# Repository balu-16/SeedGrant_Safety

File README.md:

# Smart Safety Tag

Personal-safety project: Expo / React Native client + FastAPI + PostgreSQL (Supabase) backend + React admin portal.

## Layout

- `client/` — Expo / React Native / TypeScript app (onboarding, auth, Home, Track, Guardians, Profile). See `client/README.md`.
- `server/` — FastAPI + PostgreSQL (Supabase) backend, shared by the app and the admin portal. See `server/README.md` for setup, migrations, and the API surface.
- `admin/` — React + Vite web admin portal (same design language as the app). See `admin/README.md`.
- `reference/` — original design reference images (unchanged).

Browser-test output (screenshots, traces) is generated under `client/test-results/`
and is git-ignored.

## Quick start

Frontend (mobile app):

```sh
cd client
npm install
npx expo start
```

Backend:

```sh
cd server
uv sync
cp .env.example .env   # then fill in DATABASE_URL + JWT_SECRET
uv run python -m app.db.migrate
uv run uvicorn app.main:app --reload   # http://127.0.0.1:8000
```

Admin portal (web):

```sh
cd admin
npm install
npm run dev   # http://localhost:5173, proxies /api to localhost:8000
```

## Admin portal

- Same backend, same database — the portal adds `/api/admin/*` routes guarded by a
  `role` column on `users` (fail-closed, checked per request).
- First admin: set `ADMIN_EMAILS=email@example.com` on the server (promoted at
  startup), or run `uv run python -m app.bootstrap_admin email@example.com` once.
- Features: dashboard KPIs + charts, live SOS monitor (WebSocket), full user
  control (disable / force-logout / reset-password / promote / delete), device and
  guardian management, emergency timelines on a map, location history + purge,
  push broadcasts, and a complete audit log.
- Deploy: static build (`admin/dist`) — e.g. Vercel (config included). Set
  `VITE_API_URL` to the backend URL and add the portal origin to the server's
  `CORS_ORIGINS`.

## Deploy (Render)

Root Directory: `server`. See `server/README.md` for build/start commands and env vars.

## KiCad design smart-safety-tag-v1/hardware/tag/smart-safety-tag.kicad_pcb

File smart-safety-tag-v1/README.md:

# Smart Safety Tag V1

Editable KiCad design and prototype fabrication package for a BLE safety tag and its protected pogo charging adapter. The tag uses an ESP32-S3-MINI-1-N4R2, PDM microphone, LIS2DW12, MAX17048, protected 400 mAh battery, physical SOS button, RGB LED and vibration motor. The phone supplies GPS and Internet access.

Both boards are routed and checked with KiCad 10.0.6. PCB DRC has no ignored rules, violations, unconnected items or schematic-parity findings. ERC reports have zero errors and warnings under KiCad's default checks; the four ERC diagnostics listed in each report remain ignored by KiCad. No individual ERC/DRC findings are excluded. The hardware-test application builds with ESP-IDF v5.5. **Physical prototype validation remains pending.** This package supports prototype manufacture; it does not establish product safety, radio/acoustic performance, enclosure fit or an ingress-protection rating.

| Deliverable | Location |
| --- | --- |
| Tag KiCad project, 8 hierarchical child sheets and 60 × 42 mm PCB | [hardware/tag/smart-safety-tag.kicad_pro](hardware/tag/smart-safety-tag.kicad_pro) |
| Charging adapter KiCad project and 32 × 22 mm PCB | [hardware/charging-adapter/charging-adapter.kicad_pro](hardware/charging-adapter/charging-adapter.kicad_pro) |
| Tag Gerbers/drills, BOM, placement CSVs and assembly/schematic PDFs | [manufacturing/tag](manufacturing/tag) |
| Adapter Gerbers/drills, BOM, placement CSVs and assembly/schematic PDFs | [manufacturing/charging-adapter](manufacturing/charging-adapter) |
| Component decisions, substitutions and manufacturer sources | [docs/design-inputs.md](docs/design-inputs.md) |
| Power architecture and calculated runtime scenarios | [docs/power-budget.md](docs/power-budget.md) |
| GPIO map and six-pad programming interface | [docs/gpio-map.md](docs/gpio-map.md) |
| Board fabrication and assembly specification | [docs/manufacturing-specification.md](docs/manufacturing-specification.md) |
| Power-on, charging, peripheral and qualification procedure | [docs/bring-up.md](docs/bring-up.md) |
| CAD/calculation/build evidence and pending measurements | [docs/verification.md](docs/verification.md) |
| Modular hardware-test source and prebuilt images | [firmware/hardware-tests](firmware/hardware-tests) |

Use KiCad 10.0.x or later and keep each project's `symbols/`, `footprints/`, `sym-lib-table` and `fp-lib-table` alongside its native files. All required symbols and land patterns are supplied locally. Optional 3D model references use KiCad's standard model libraries; external STEP models are not bundled. A PCB 3D view does not validate the proposed enclosure or cell clearances.

The main electrical substitutions are TPS63802 for TPS63031 to increase the converter current margin, TPD1E10B06 for the proposed charging ESD diode, and switched 3.0 V supplies for the microphone and motor. An analog NTC window independently inhibits charging. The charging adapter includes a USB-C power input and eFuse before its exposed spring pins. Read the design decisions and fabrication notes before purchasing or assembly.

The tag has 83 PCB footprints, including six programming pads, two bare charging contacts and a wired motor. RT1 is fitted on the rear. The battery is an off-board BOM item and must be insulated and thermally coupled to RT1 as documented. Both boards are 1.0 mm thick; the adapter's USB connector requires 1.0 ±0.10 mm. The module's antenna projects beyond the tag outline and its keepout must remain clear of the battery, clip and magnets.

Each manufacturing directory has a bare-board ZIP and `manifest.json` linking exported files to the complete editable CAD source using SHA-256 hashes. Assembly CSVs use KiCad coordinates/rotations; read the manufacturing specification before importing them. The fabrication ZIP also contains the manufacturing notes.

To regenerate checks and exports from the project root:

```sh
python3 -m pip install -r scripts/requirements.txt
python3 scripts/generate_gpio_header.py
python3 scripts/check_thermal_window.py
python3 scripts/export_manufacturing.py --cli-command kicad-cli
python3 scripts/package_release.py
```

Placement and schematic-generation scripts are construction tools. Rerunning a placement script replaces the corresponding layout, so preserve the routed board and review changes before doing that. GPIO assignments originate in `hardware/board-interface.json`; electrical components and pin/net definitions originate in `scripts/circuit_data.py`, `adapter_data.py`, `parts.py` and `passive_parts.py`.

The included firmware captures audio and checks peripherals. Keyword inference, a custom emergency BLE service, smartphone messaging and sleep/wake behavior need application firmware and physical validation. Continuous keyword detection does not operate in deep sleep in this design.

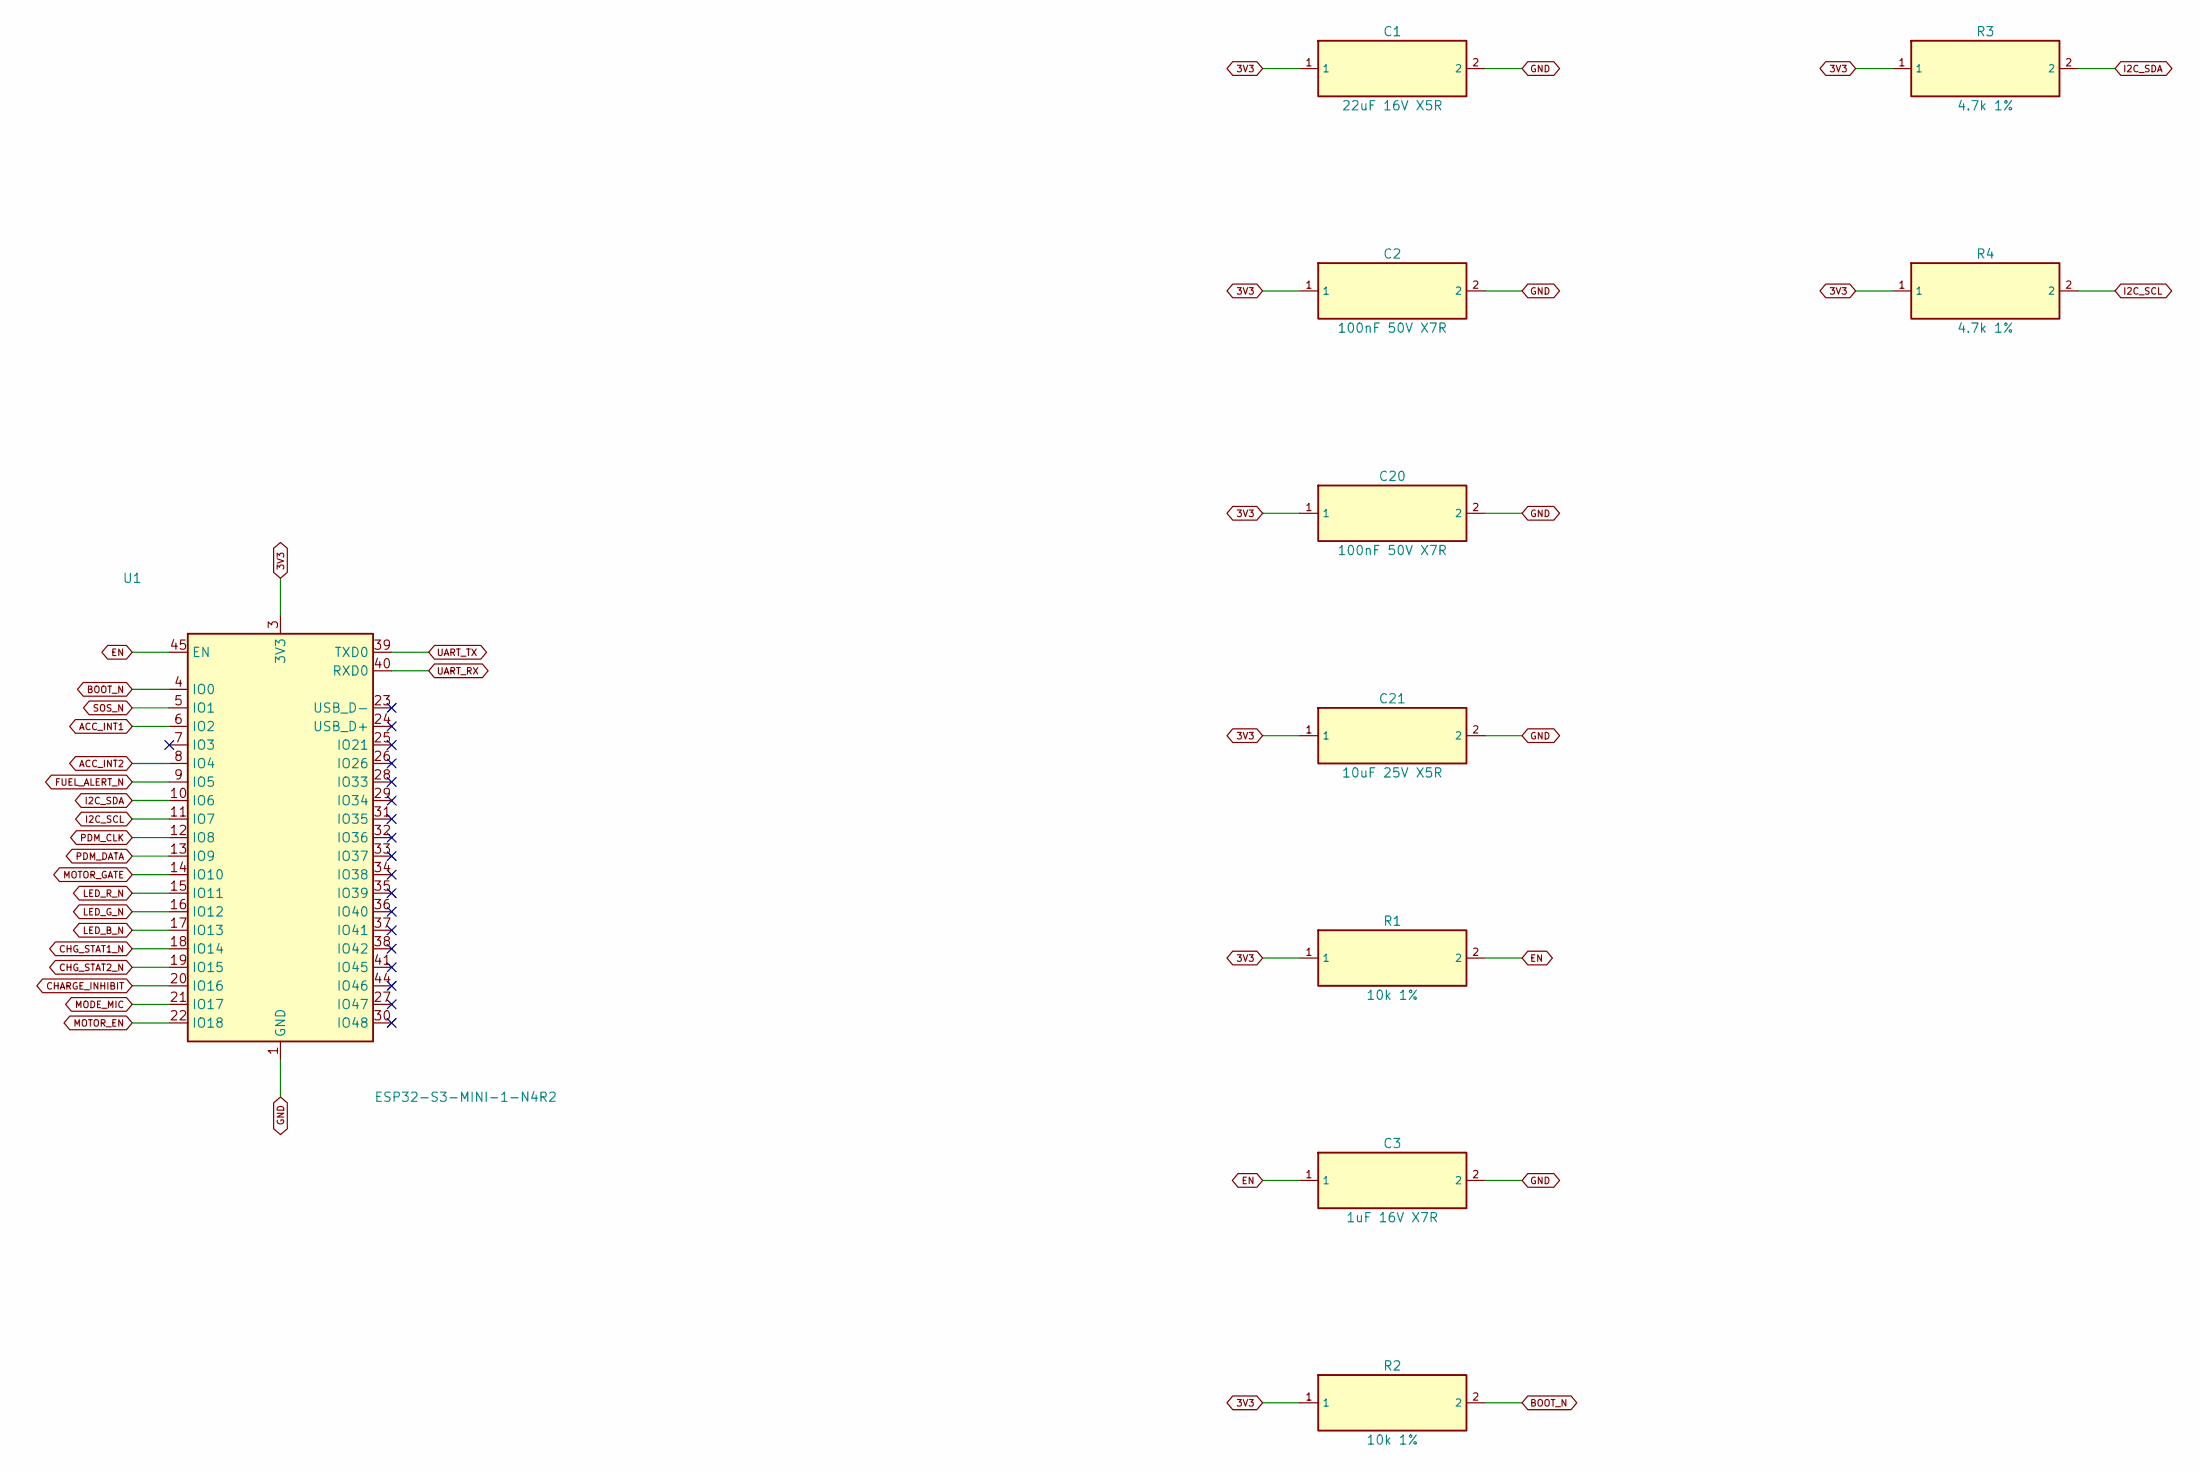
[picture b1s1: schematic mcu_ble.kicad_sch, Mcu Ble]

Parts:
C1: 22uF 16V X5R; C_1206_3216Metric; MPN C3216X5R1C226M160AB
C2, C20: 100nF 50V X7R; C_0603_1608Metric; MPN C1608X7R1H104K080AA
C3: 1uF 16V X7R; C_0603_1608Metric; MPN C1608X7R1C105K080AC
C21: 10uF 25V X5R; C_0805_2012Metric; MPN C2012X5R1E106K125AB
R1, R2: 10k 1%; R_0603_1608Metric; MPN RC0603FR-0710KL
R3, R4: 4.7k 1%; R_0603_1608Metric; MPN RC0603FR-074K7L
U1: ESP32-S3-MINI-1-N4R2; ESP32-S2-MINI-1; MPN ESP32-S3-MINI-1-N4R2

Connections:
3V3: C1.1, C2.1, C20.1, C21.1, R1.1, R2.1, R3.1, R4.1, U1.3 (3V3); also elsewhere on the board
ACC_INT1: U1.6 (IO2); also elsewhere on the board
ACC_INT2: U1.8 (IO4); also elsewhere on the board
BOOT_N: R2.2, U1.4 (IO0); also elsewhere on the board
CHARGE_INHIBIT: U1.20 (IO16); also elsewhere on the board
CHG_STAT1_N: U1.18 (IO14); also elsewhere on the board
CHG_STAT2_N: U1.19 (IO15); also elsewhere on the board
EN: C3.1, R1.2, U1.45 (EN); also elsewhere on the board
FUEL_ALERT_N: U1.9 (IO5); also elsewhere on the board
GND: C1.2, C2.2, C3.2, C20.2, C21.2, U1.1 (GND), U1.2 (GND), U1.42 (GND), U1.43 (GND), U1.46 (GND), U1.47 (GND), U1.48 (GND), U1.49 (GND), U1.50 (GND), U1.51 (GND), U1.52 (GND), U1.53 (GND), U1.54 (GND), U1.55 (GND), U1.56 (GND), U1.57 (GND), U1.58 (GND), U1.59 (GND), U1.60 (GND), U1.61 (GND), U1.62 (GND), U1.63 (GND), U1.64 (GND), U1.65 (GND); also elsewhere on the board
I2C_SCL: R4.2, U1.11 (IO7); also elsewhere on the board
I2C_SDA: R3.2, U1.10 (IO6); also elsewhere on the board
LED_B_N: U1.17 (IO13); also elsewhere on the board
LED_G_N: U1.16 (IO12); also elsewhere on the board
LED_R_N: U1.15 (IO11); also elsewhere on the board
MODE_MIC: U1.21 (IO17); also elsewhere on the board
MOTOR_EN: U1.22 (IO18); also elsewhere on the board
MOTOR_GATE: U1.14 (IO10); also elsewhere on the board
PDM_CLK: U1.12 (IO8); also elsewhere on the board
PDM_DATA: U1.13 (IO9); also elsewhere on the board
SOS_N: U1.5 (IO1); also elsewhere on the board
UART_RX: U1.40 (RXD0); also elsewhere on the board
UART_TX: U1.39 (TXD0); also elsewhere on the board

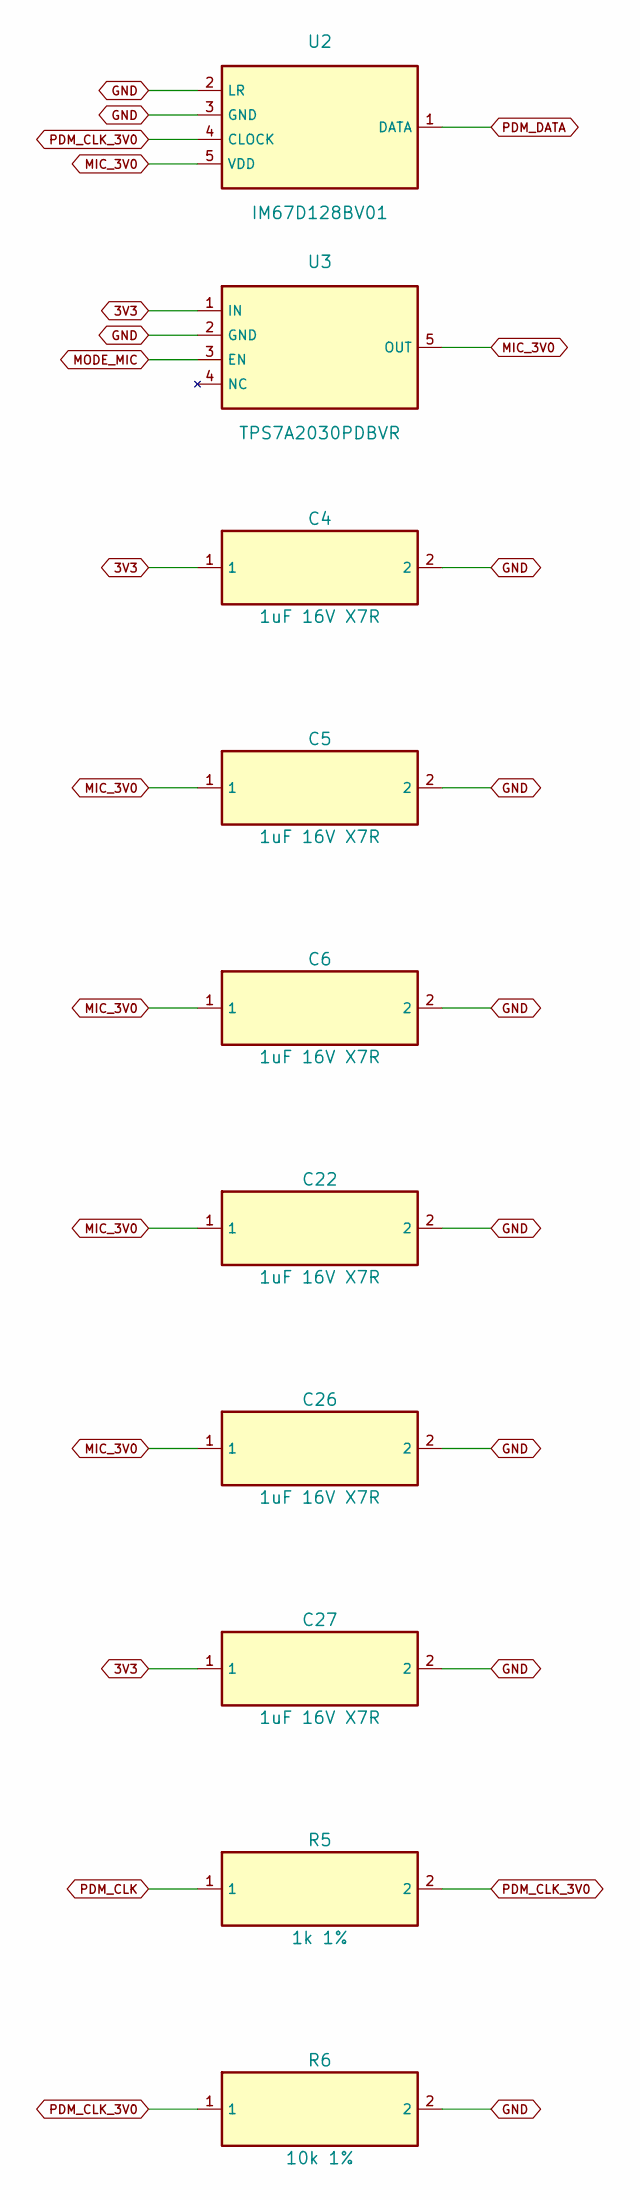
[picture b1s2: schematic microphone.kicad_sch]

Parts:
C4, C5, C6, C22, C26, C27: 1uF 16V X7R; C_0603_1608Metric; MPN C1608X7R1C105K080AC
R5: 1k 1%; R_0603_1608Metric; MPN RC0603FR-071KL
R6: 10k 1%; R_0603_1608Metric; MPN RC0603FR-0710KL
U2: IM67D128BV01; Infineon_IM67D128BV01; MPN IM67D128BV01
U3: TPS7A2030PDBVR; SOT-23-5; MPN TPS7A2030PDBVR

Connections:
3V3: C4.1, C27.1, U3.1 (IN); also elsewhere on the board
GND: C4.2, C5.2, C6.2, C22.2, C26.2, C27.2, R6.2, U2.2 (LR), U2.3 (GND), U3.2 (GND); also elsewhere on the board
MIC_3V0: C5.1, C6.1, C22.1, C26.1, U2.5 (VDD), U3.5 (OUT)
MODE_MIC: U3.3 (EN); also elsewhere on the board
PDM_CLK: R5.1; also elsewhere on the board
PDM_CLK_3V0: R5.2, R6.1, U2.4 (CLOCK)
PDM_DATA: U2.1 (DATA); also elsewhere on the board

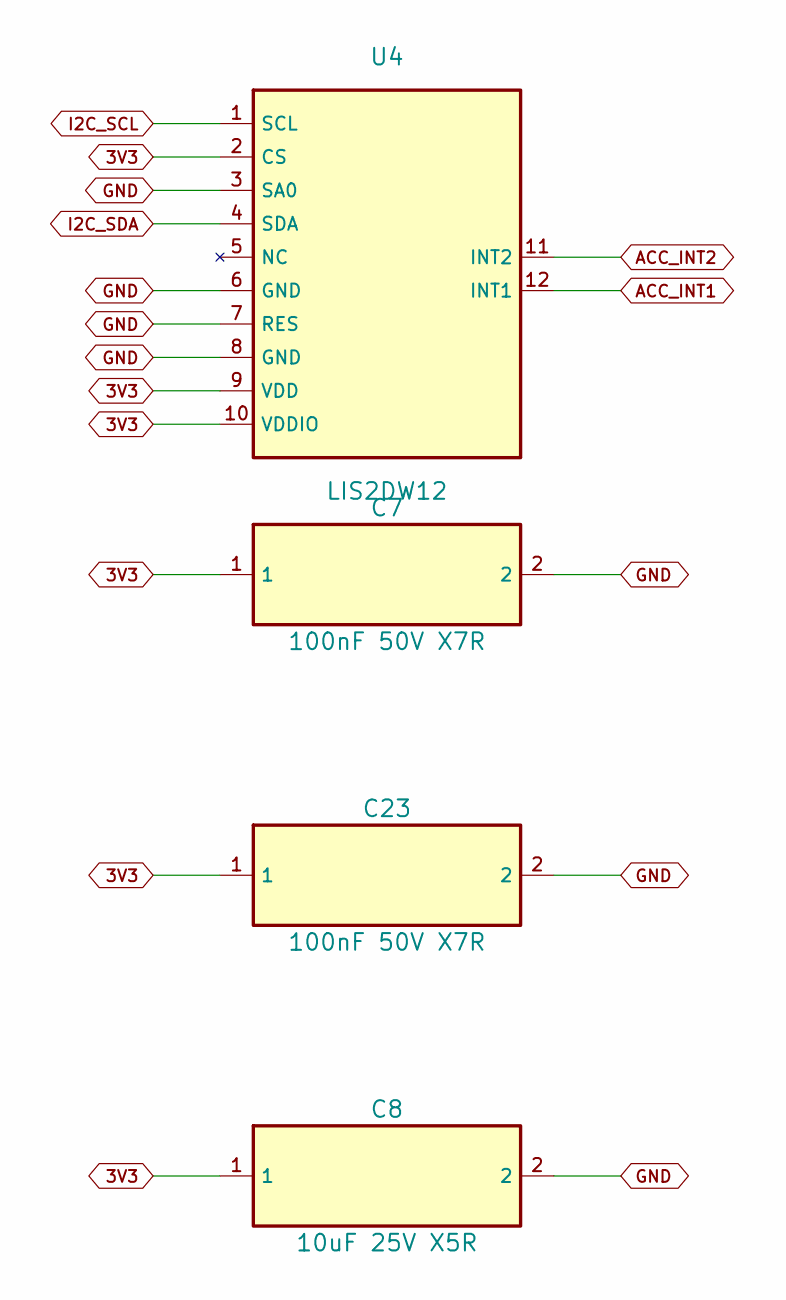
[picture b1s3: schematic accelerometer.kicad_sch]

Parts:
C7, C23: 100nF 50V X7R; C_0603_1608Metric; MPN C1608X7R1H104K080AA
C8: 10uF 25V X5R; C_0805_2012Metric; MPN C2012X5R1E106K125AB
U4: LIS2DW12; LGA-12_2x2mm_P0.5mm; MPN LIS2DW12TR

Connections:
3V3: C7.1, C8.1, C23.1, U4.2 (CS), U4.9 (VDD), U4.10 (VDDIO); also elsewhere on the board
ACC_INT1: U4.12 (INT1); also elsewhere on the board
ACC_INT2: U4.11 (INT2); also elsewhere on the board
GND: C7.2, C8.2, C23.2, U4.3 (SA0), U4.6 (GND), U4.7 (RES), U4.8 (GND); also elsewhere on the board
I2C_SCL: U4.1 (SCL); also elsewhere on the board
I2C_SDA: U4.4 (SDA); also elsewhere on the board

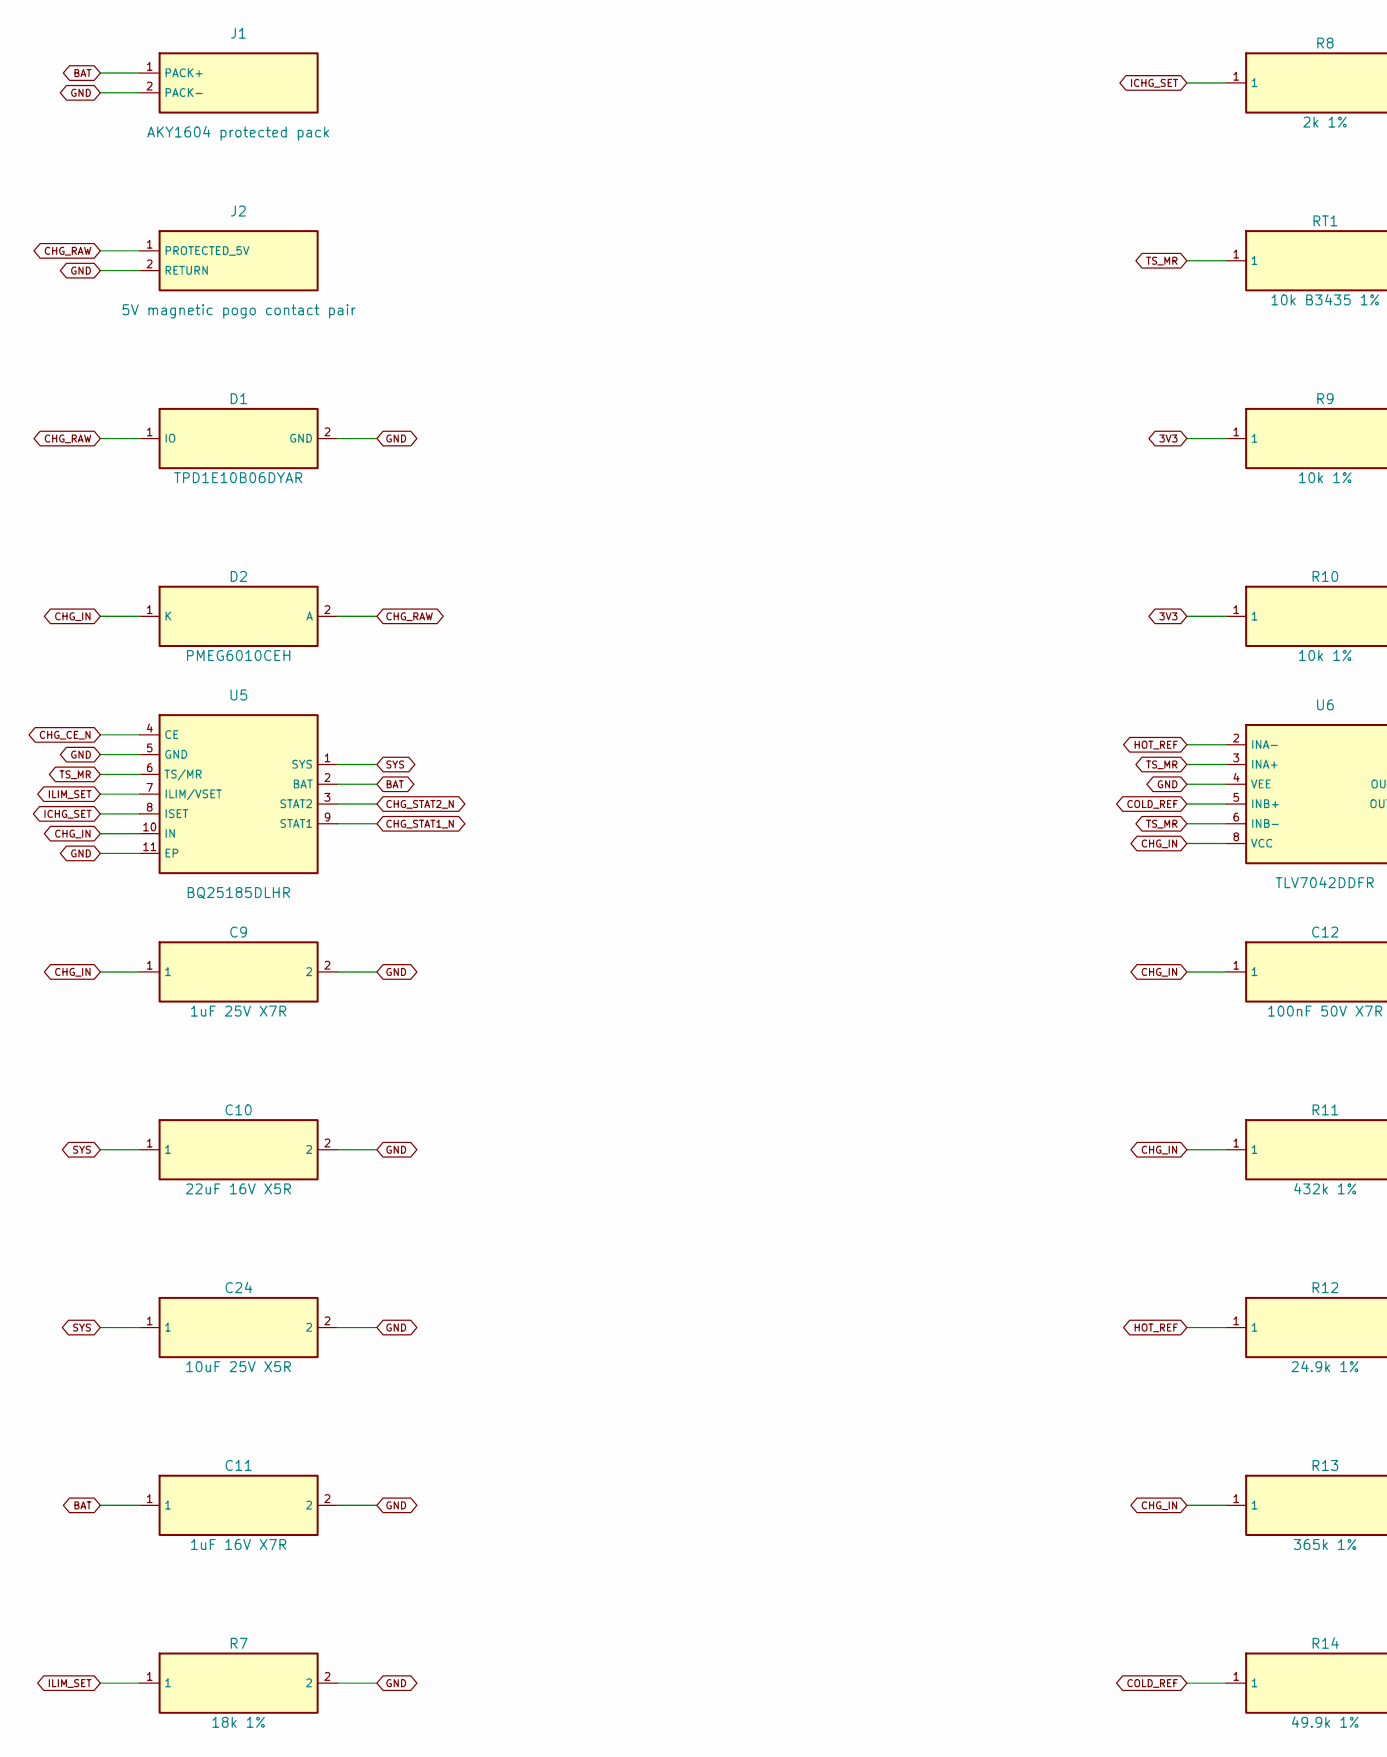
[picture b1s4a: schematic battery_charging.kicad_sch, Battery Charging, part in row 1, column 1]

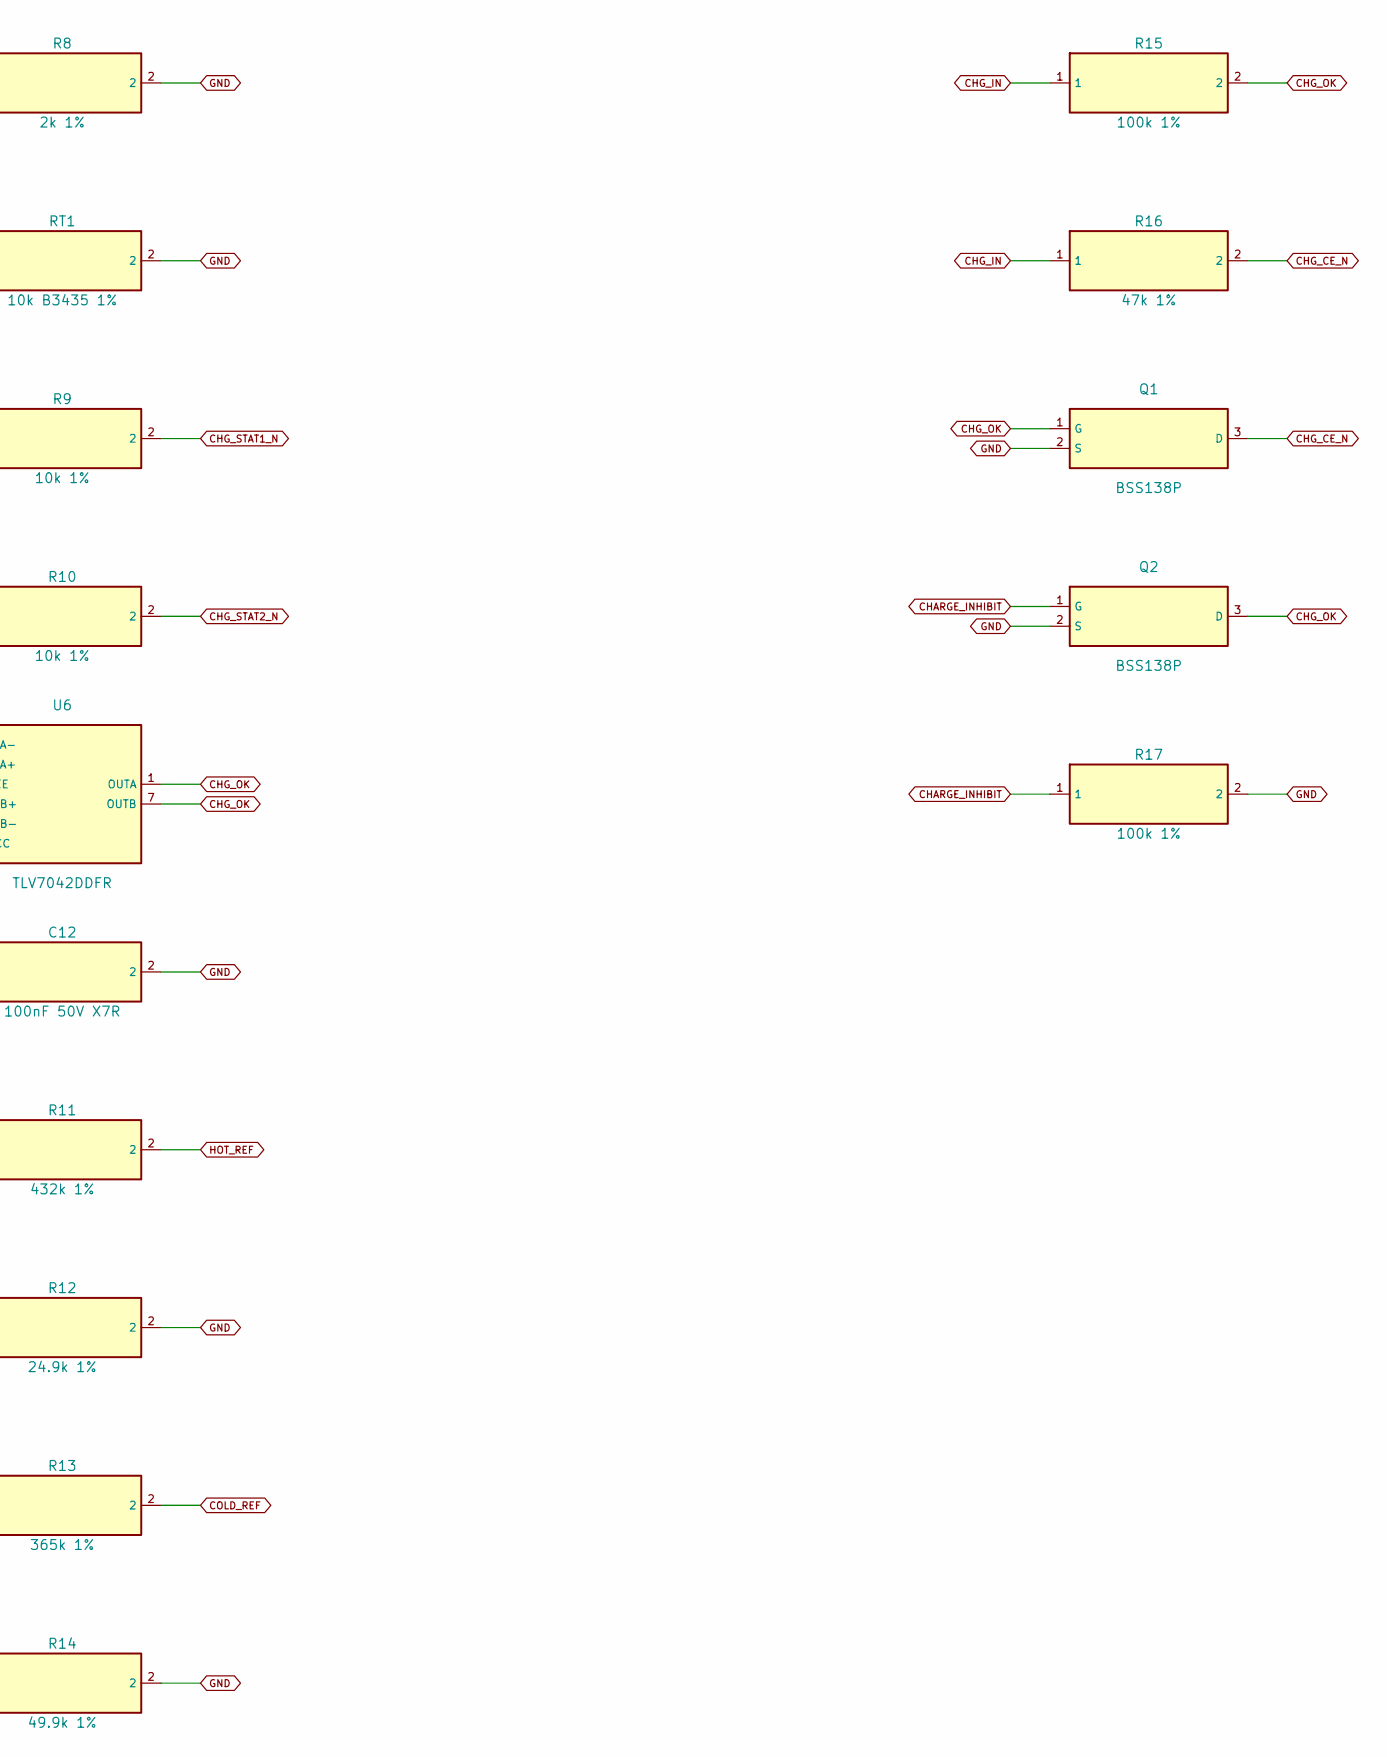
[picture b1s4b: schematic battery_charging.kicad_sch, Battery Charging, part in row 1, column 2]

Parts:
C9: 1uF 25V X7R; C_0603_1608Metric; MPN C1608X7R1E105K080AE
C10: 22uF 16V X5R; C_1206_3216Metric; MPN C3216X5R1C226M160AB
C11: 1uF 16V X7R; C_0603_1608Metric; MPN C1608X7R1C105K080AC
C12: 100nF 50V X7R; C_0603_1608Metric; MPN C1608X7R1H104K080AA
C24: 10uF 25V X5R; C_0805_2012Metric; MPN C2012X5R1E106K125AB
D1: TPD1E10B06DYAR; D_SOD-523; MPN TPD1E10B06DYAR
D2: PMEG6010CEH; D_SOD-123F; MPN PMEG6010CEH,115
J1: AKY1604 protected pack; Molex_PicoBlade_53261-0271_1x02-1MP_P1.25mm_Horizontal; MPN 53261-0271
J2: 5V magnetic pogo contact pair; Pogo_Charge_2Pin
Q1, Q2: BSS138P; SOT-23; MPN BSS138P,215
R7: 18k 1%; R_0603_1608Metric; MPN RC0603FR-0718KL
R8: 2k 1%; R_0603_1608Metric; MPN RC0603FR-072KL
R9, R10: 10k 1%; R_0603_1608Metric; MPN RC0603FR-0710KL
R11: 432k 1%; R_0603_1608Metric; MPN RC0603FR-07432KL
R12: 24.9k 1%; R_0603_1608Metric; MPN RC0603FR-0724K9L
R13: 365k 1%; R_0603_1608Metric; MPN RC0603FR-07365KL
R14: 49.9k 1%; R_0603_1608Metric; MPN RC0603FR-0749K9L
R15, R17: 100k 1%; R_0603_1608Metric; MPN RC0603FR-07100KL
R16: 47k 1%; R_0603_1608Metric; MPN RC0603FR-0747KL
RT1: 10k B3435 1%; R_0603_1608Metric; MPN B57332V5103A260
U5: BQ25185DLHR; Texas_DLH0010A_WSON-10-1EP_2.2x2mm_P0.4mm_EP0.9x1.5mm; MPN BQ25185DLHR
U6: TLV7042DDFR; SOT-23-8; MPN TLV7042DDFR

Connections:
3V3: R9.1, R10.1; also elsewhere on the board
BAT: C11.1, J1.1 (PACK+), U5.2 (BAT); also elsewhere on the board
CHARGE_INHIBIT: Q2.1 (G), R17.1; also elsewhere on the board
CHG_CE_N: Q1.3 (D), R16.2, U5.4 (CE)
CHG_IN: C9.1, C12.1, D2.1 (K), R11.1, R13.1, R15.1, R16.1, U5.10 (IN), U6.8 (VCC)
CHG_OK: Q1.1 (G), Q2.3 (D), R15.2, U6.1 (OUTA), U6.7 (OUTB)
CHG_RAW: D1.1 (IO), D2.2 (A), J2.1 (PROTECTED_5V)
CHG_STAT1_N: R9.2, U5.9 (STAT1); also elsewhere on the board
CHG_STAT2_N: R10.2, U5.3 (STAT2); also elsewhere on the board
COLD_REF: R13.2, R14.1, U6.5 (INB+)
GND: C9.2, C10.2, C11.2, C12.2, C24.2, D1.2 (GND), J1.2 (PACK-), J2.2 (RETURN), Q1.2 (S), Q2.2 (S), R7.2, R8.2, R12.2, R14.2, R17.2, RT1.2, U5.5 (GND), U5.11 (EP), U6.4 (VEE); also elsewhere on the board
HOT_REF: R11.2, R12.1, U6.2 (INA-)
ICHG_SET: R8.1, U5.8 (ISET)
ILIM_SET: R7.1, U5.7 (ILIM/VSET)
SYS: C10.1, C24.1, U5.1 (SYS); also elsewhere on the board
TS_MR: RT1.1, U5.6 (TS/MR), U6.3 (INA+), U6.6 (INB-)

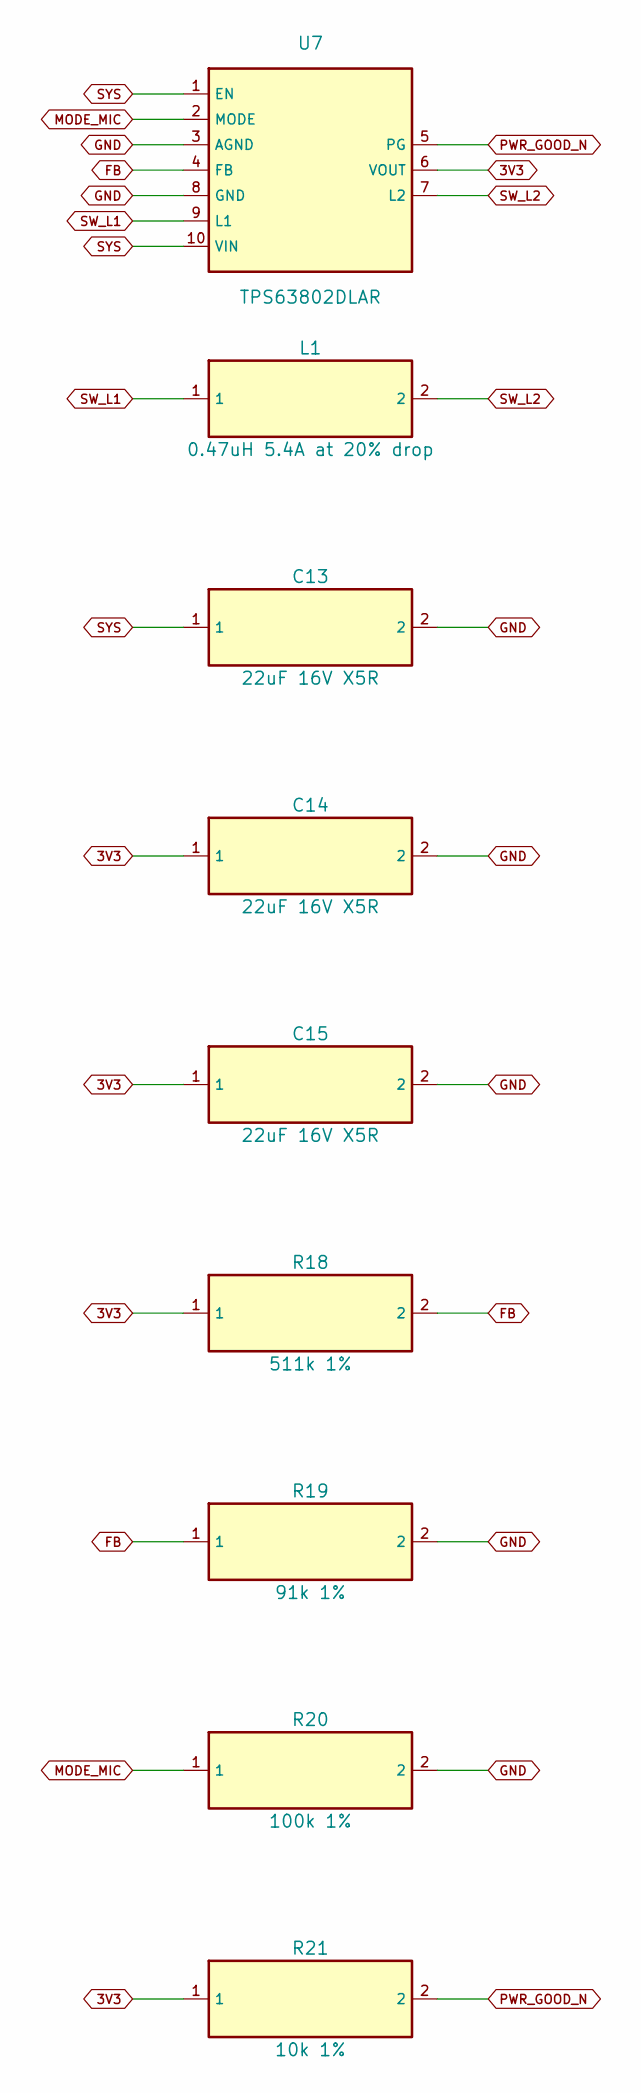
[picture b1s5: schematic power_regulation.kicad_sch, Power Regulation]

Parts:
C13, C14, C15: 22uF 16V X5R; C_1206_3216Metric; MPN C3216X5R1C226M160AB
L1: 0.47uH 5.4A at 20% drop; L_Coilcraft_XFL4015; MPN XFL4015-471MEC
R18: 511k 1%; R_0603_1608Metric; MPN RC0603FR-07511KL
R19: 91k 1%; R_0603_1608Metric; MPN RC0603FR-0791KL
R20: 100k 1%; R_0603_1608Metric; MPN RC0603FR-07100KL
R21: 10k 1%; R_0603_1608Metric; MPN RC0603FR-0710KL
U7: TPS63802DLAR; Texas_DLA0010A_VSON-10_2x3mm; MPN TPS63802DLAR

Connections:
3V3: C14.1, C15.1, R18.1, R21.1, U7.6 (VOUT); also elsewhere on the board
FB: R18.2, R19.1, U7.4 (FB)
GND: C13.2, C14.2, C15.2, R19.2, R20.2, U7.3 (AGND), U7.8 (GND); also elsewhere on the board
MODE_MIC: R20.1, U7.2 (MODE); also elsewhere on the board
PWR_GOOD_N: R21.2, U7.5 (PG)
SW_L1: L1.1, U7.9 (L1)
SW_L2: L1.2, U7.7 (L2)
SYS: C13.1, U7.1 (EN), U7.10 (VIN); also elsewhere on the board

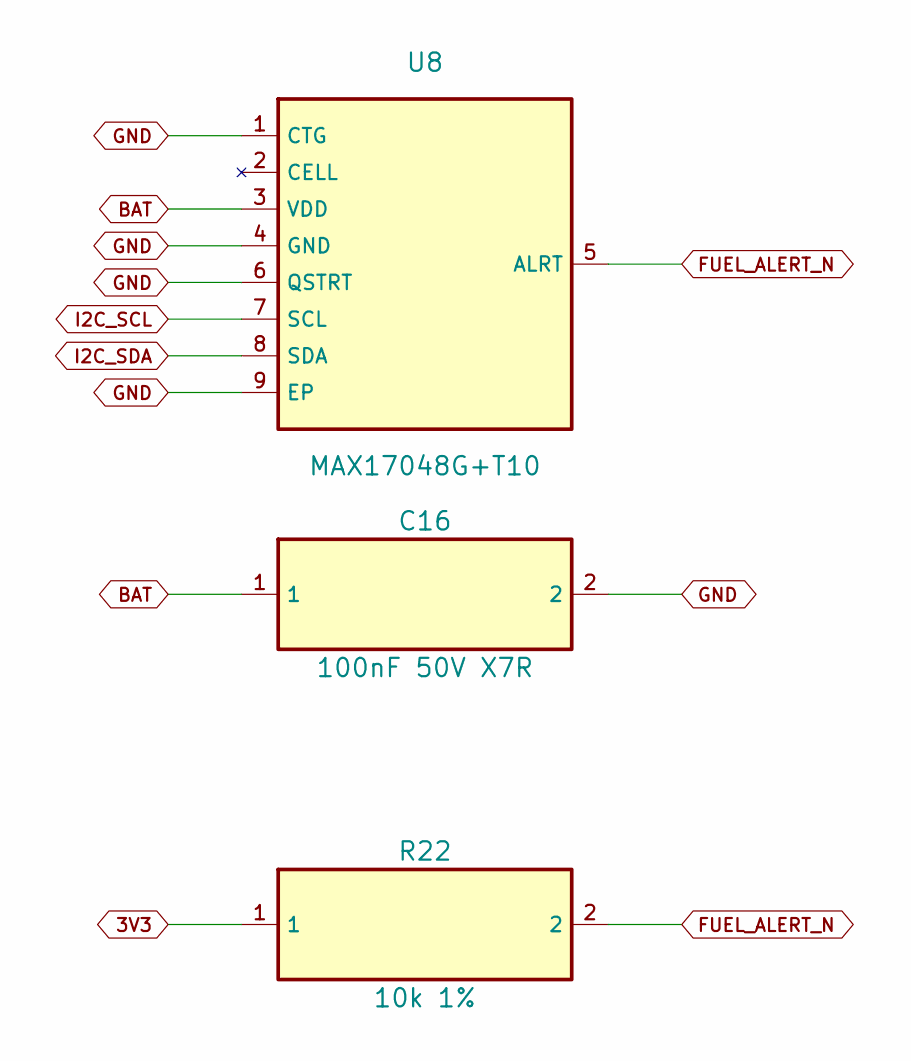
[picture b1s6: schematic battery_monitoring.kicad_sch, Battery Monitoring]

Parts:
C16: 100nF 50V X7R; C_0603_1608Metric; MPN C1608X7R1H104K080AA
R22: 10k 1%; R_0603_1608Metric; MPN RC0603FR-0710KL
U8: MAX17048G+T10; TDFN-8-1EP_2x2mm_P0.5mm_EP0.8x1.2mm; MPN MAX17048G+T10

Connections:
3V3: R22.1; also elsewhere on the board
BAT: C16.1, U8.3 (VDD); also elsewhere on the board
FUEL_ALERT_N: R22.2, U8.5 (ALRT); also elsewhere on the board
GND: C16.2, U8.1 (CTG), U8.4 (GND), U8.6 (QSTRT), U8.9 (EP); also elsewhere on the board
I2C_SCL: U8.7 (SCL); also elsewhere on the board
I2C_SDA: U8.8 (SDA); also elsewhere on the board
